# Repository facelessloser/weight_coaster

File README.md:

# weight_coaster
Ever wanted a coaster that lights up depending on how much drinks in your glass, Built with an arduino a ws2812 and a load cell

Blog post - https://facelesstech.wordpress.com/2017/09/17/weight-coaster/
Youtube video - https://www.youtube.com/watch?v=xiPBg8h8AEU

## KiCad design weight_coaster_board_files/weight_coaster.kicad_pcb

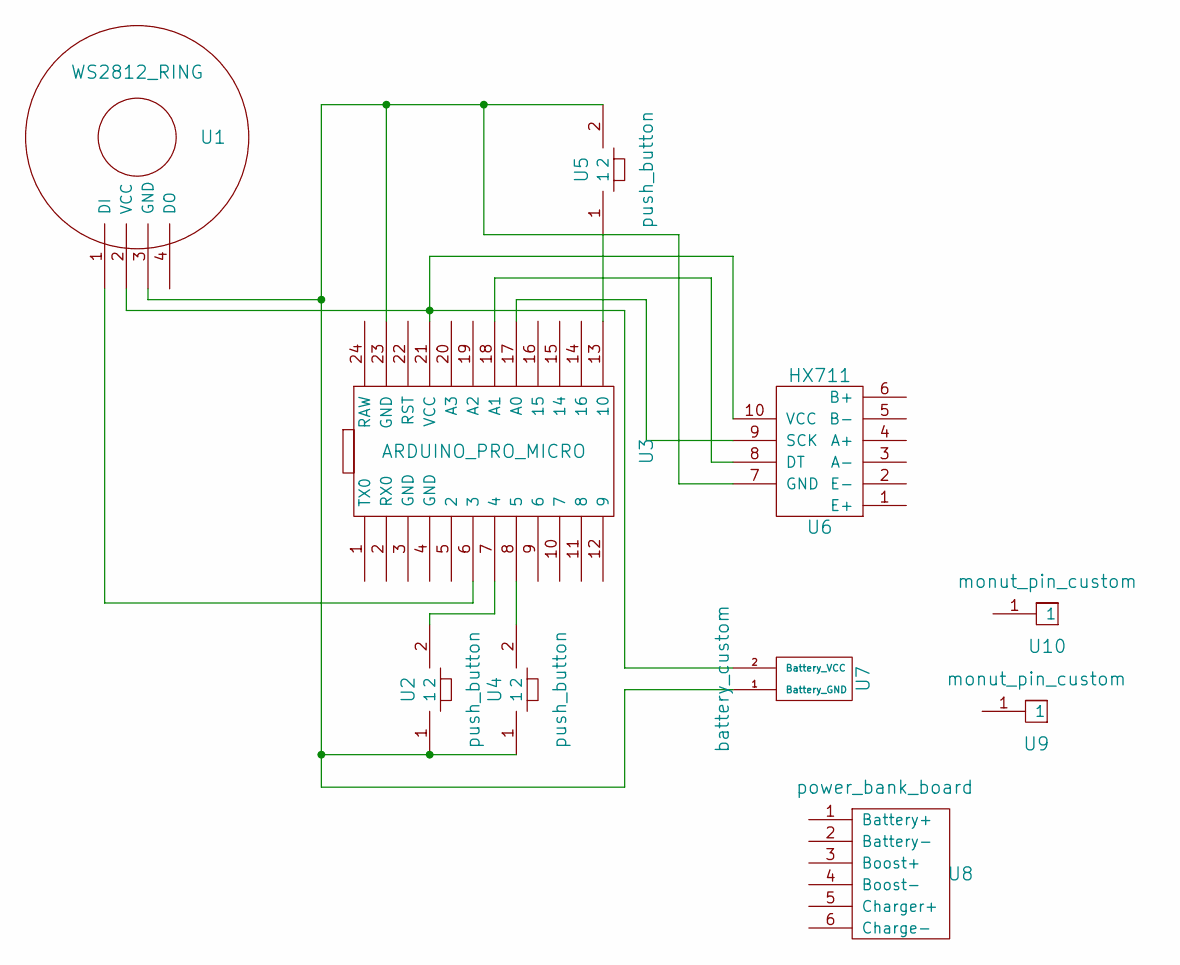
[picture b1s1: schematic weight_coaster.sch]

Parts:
U1: WS2812_RING; ws2812_custom
U2, U4, U5: push_button; small_button_2pin_custom
U3: ARDUINO_PRO_MICRO; arduino_leonardo
U6: HX711; hx711
U7: battery_custom; Power_connector
U8: power_bank_board; pound_shop_power_bank_custom
U9, U10: monut_pin_custom; mount_pin_custom

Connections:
unnamed: U1.1 (DI), U3.6 (3)
unnamed: U1.2 (VCC), U3.21 (VCC), U6.10 (VCC), U7.2 (Battery_VCC)
unnamed: U1.3 (GND), U2.1, U3.23 (GND), U4.1, U5.2, U6.7 (GND), U7.1 (Battery_GND)
unnamed: U2.2, U3.7 (4)
unnamed: U3.8 (5), U4.2
unnamed: U3.13 (10), U5.1
unnamed: U3.17 (A0), U6.9 (SCK)
unnamed: U3.18 (A1), U6.8 (DT)

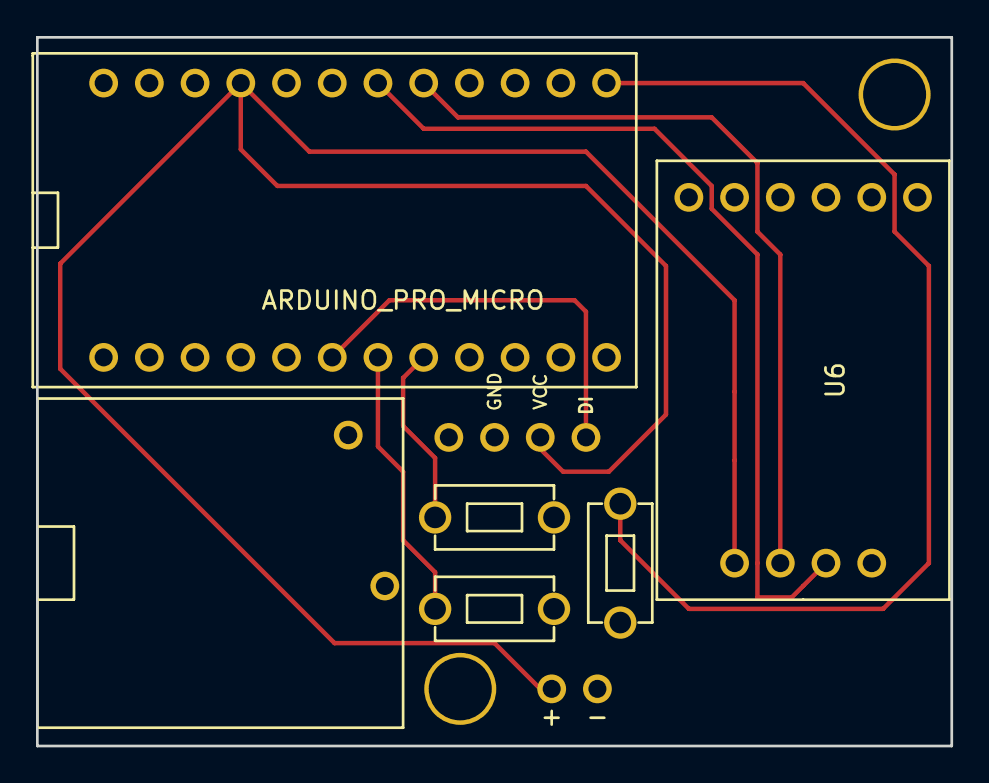
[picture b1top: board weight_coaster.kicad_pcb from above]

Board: 2 copper layers, 50.8 x 39.4 mm, 10 parts (0 on the bottom side), 8 nets.

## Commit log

2017-09-16 First upload of the finished files
2017-09-17 added links to blog post and youtube
